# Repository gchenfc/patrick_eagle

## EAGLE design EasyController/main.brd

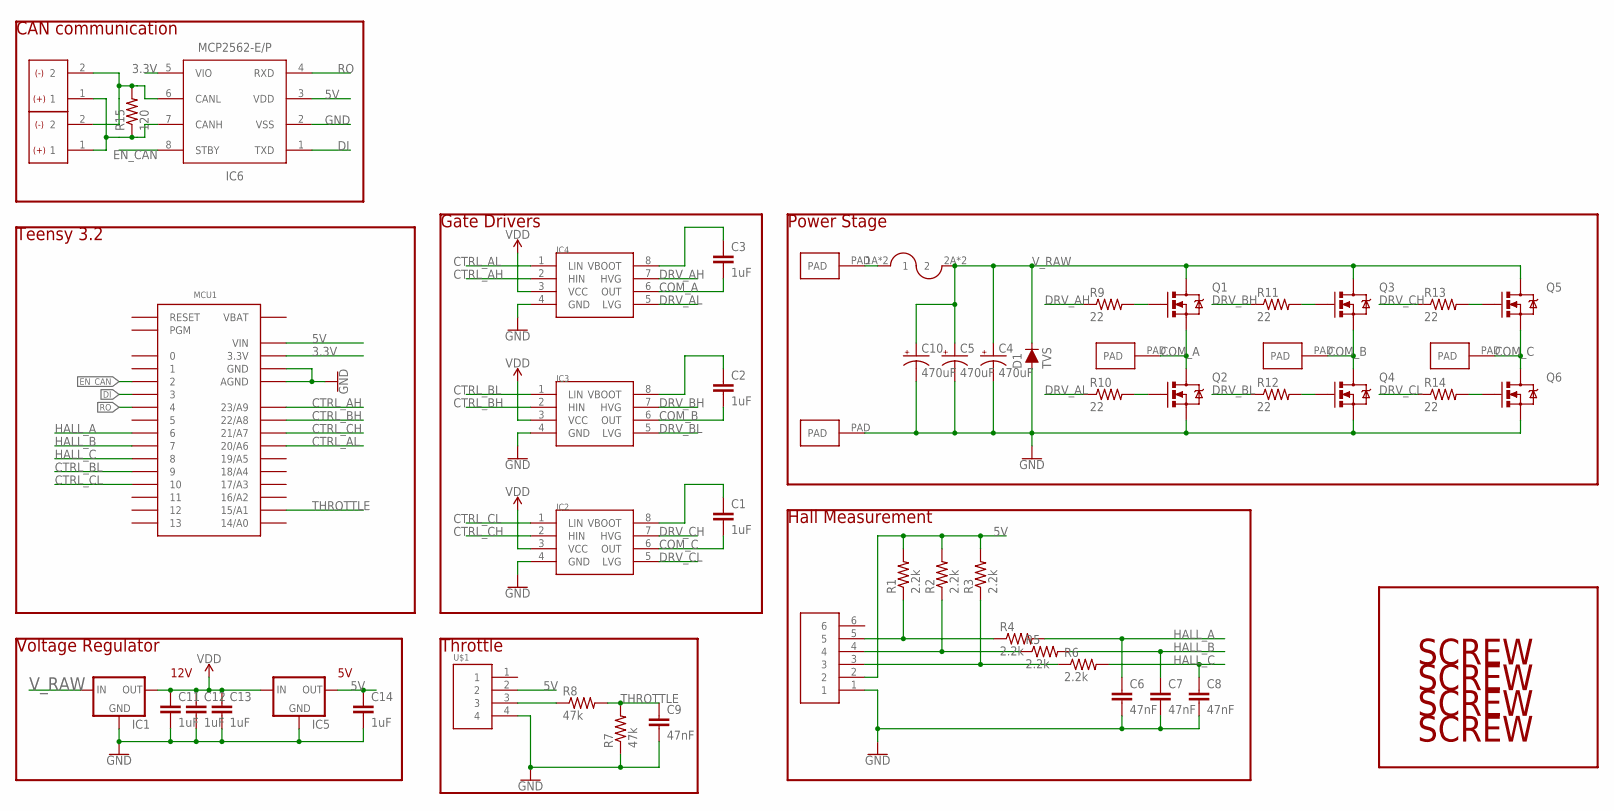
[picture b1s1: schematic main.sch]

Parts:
C1, C2, C3, C11, C12, C13, C14: 1uF; CAP-PTH-SMALL-KIT
C4, C5, C10: 470uF; CPOL-RADIAL-5MM-10MM
C6, C7, C8, C9: 47nF; CAP-PTH-SMALL-KIT
CAN1, CAN2: HEADER2; 2PINVALULOK
D1: TVS; DIODE-1N4001
IC1: V_REG_78XX; V78W_BACKWARDS
IC2, IC3, IC4: L6387EDIP8; DIP762W53P254L1092H508Q8B
IC5: V_REG_78XXTO-92_UNTESTED; TO-92
IC6: MCP2562-E/P; PDIP8_300MC
J3: FUSE; AUTO_FUSE
MCU1: TEENSY_3.0_BASIC
Q1, Q2, Q3, Q4, Q5, Q6: MOSFET-NCHANNELTO-220-FLAT; TO-220-FLAT
R1, R2, R3, R4, R5, R6: 2.2k; AXIAL-0.3
R7, R8: 47k; AXIAL-0.3
R9, R10, R11, R12, R13, R14: 22; AXIAL-0.3
R15: 120; AXIAL-0.3
U$1: HEADER4VALULOK; 4PINVALULOK
U$2: HEADER6; 6PINVALULOK
U$4, U$5, U$6, U$7, U$8: PAD
U$10, U$11, U$12, U$13: SCREW; M3HOLE

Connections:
3.3V: IC6.5 (VIO), MCU1.3.3V, MCU1.3.3V1 (3.3V)
5V: C14.1, IC5.1 (OUT), IC6.3 (VDD), MCU1.VIN, R1.P$2 (2), R2.P$2 (2), R3.P$2 (2), U$1.2, U$2.2
CANH: CAN1.1, CAN2.1, IC6.7 (CANH), R15.P$1 (1)
CANL: CAN1.2, CAN2.2, IC6.6 (CANL), R15.P$2 (2)
COM_A: C3.2, IC4.6 (OUT), Q1.3 (S), Q2.2 (D), Q2.PAD (D), U$6.PAD
COM_B: C2.2, IC3.6 (OUT), Q3.3 (S), Q4.2 (D), Q4.PAD (D), U$7.PAD
COM_C: C1.2, IC2.6 (OUT), Q5.3 (S), Q6.2 (D), Q6.PAD (D), U$8.PAD
CTRL_AH: IC4.2 (HIN), MCU1.23/A9
CTRL_AL: IC4.1 (LIN), MCU1.20/A6
CTRL_BH: IC3.2 (HIN), MCU1.22/A8
CTRL_BL: IC3.1 (LIN), MCU1.9
CTRL_CH: IC2.2 (HIN), MCU1.21/A7
CTRL_CL: IC2.1 (LIN), MCU1.10
DI: IC6.1 (TXD), MCU1.3
DRV_AH: IC4.7 (HVG), R9.P$1 (1)
DRV_AL: IC4.5 (LVG), R10.P$1 (1)
DRV_BH: IC3.7 (HVG), R11.P$1 (1)
DRV_BL: IC3.5 (LVG), R12.P$1 (1)
DRV_CH: IC2.7 (HVG), R13.P$1 (1)
DRV_CL: IC2.5 (LVG), R14.P$1 (1)
EN_CAN: IC6.8 (STBY), MCU1.2
GND: C4.-, C5.-, C6.2, C7.2, C8.2, C9.2, C10.-, C11.2, C12.2, C13.2, C14.2, D1.A, IC1.GND, IC2.4 (GND), IC3.4 (GND), IC4.4 (GND), IC5.2 (GND), IC6.2 (VSS), MCU1.AGND, MCU1.GND, MCU1.GND1 (GND), Q2.3 (S), Q4.3 (S), Q6.3 (S), R7.P$1 (1), U$1.4, U$2.1, U$5.PAD
HALL_A: C6.1, MCU1.6, R4.P$2 (2)
HALL_B: C7.1, MCU1.7, R5.P$2 (2)
HALL_C: C8.1, MCU1.8, R6.P$2 (2)
unnamed: C1.1, IC2.8 (VBOOT)
unnamed: R3.P$1 (1), R6.P$1 (1), U$2.3
unnamed: C2.1, IC3.8 (VBOOT)
unnamed: R2.P$1 (1), R5.P$1 (1), U$2.4
unnamed: C3.1, IC4.8 (VBOOT)
unnamed: R1.P$1 (1), R4.P$1 (1), U$2.5
unnamed: R8.P$1 (1), U$1.3
unnamed: Q1.1 (G), R9.P$2 (2)
unnamed: Q2.1 (G), R10.P$2 (2)
unnamed: Q3.1 (G), R11.P$2 (2)
unnamed: Q4.1 (G), R12.P$2 (2)
unnamed: Q5.1 (G), R13.P$2 (2)
unnamed: Q6.1 (G), R14.P$2 (2)
RO: IC6.4 (RXD), MCU1.4
THROTTLE: C9.1, MCU1.15/A1, R7.P$2 (2), R8.P$2 (2)
VBAT: MCU1.VBAT
VDD: C11.1, C12.1, C13.1, IC1.OUT, IC2.3 (VCC), IC3.3 (VCC), IC4.3 (VCC), IC5.3 (IN)
V_PREFUSE: J3.1A (1), J3.1B (1), U$4.PAD
V_RAW: C4.+, C5.+, C10.+, D1.C, IC1.IN, J3.2A (2), J3.2B (2), Q1.2 (D), Q1.PAD (D), Q3.2 (D), Q3.PAD (D), Q5.2 (D), Q5.PAD (D)

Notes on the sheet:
Power Stage
Hall Measurement
Gate Drivers
Throttle
Teensy 3.2
Voltage Regulator
12V
CAN communication

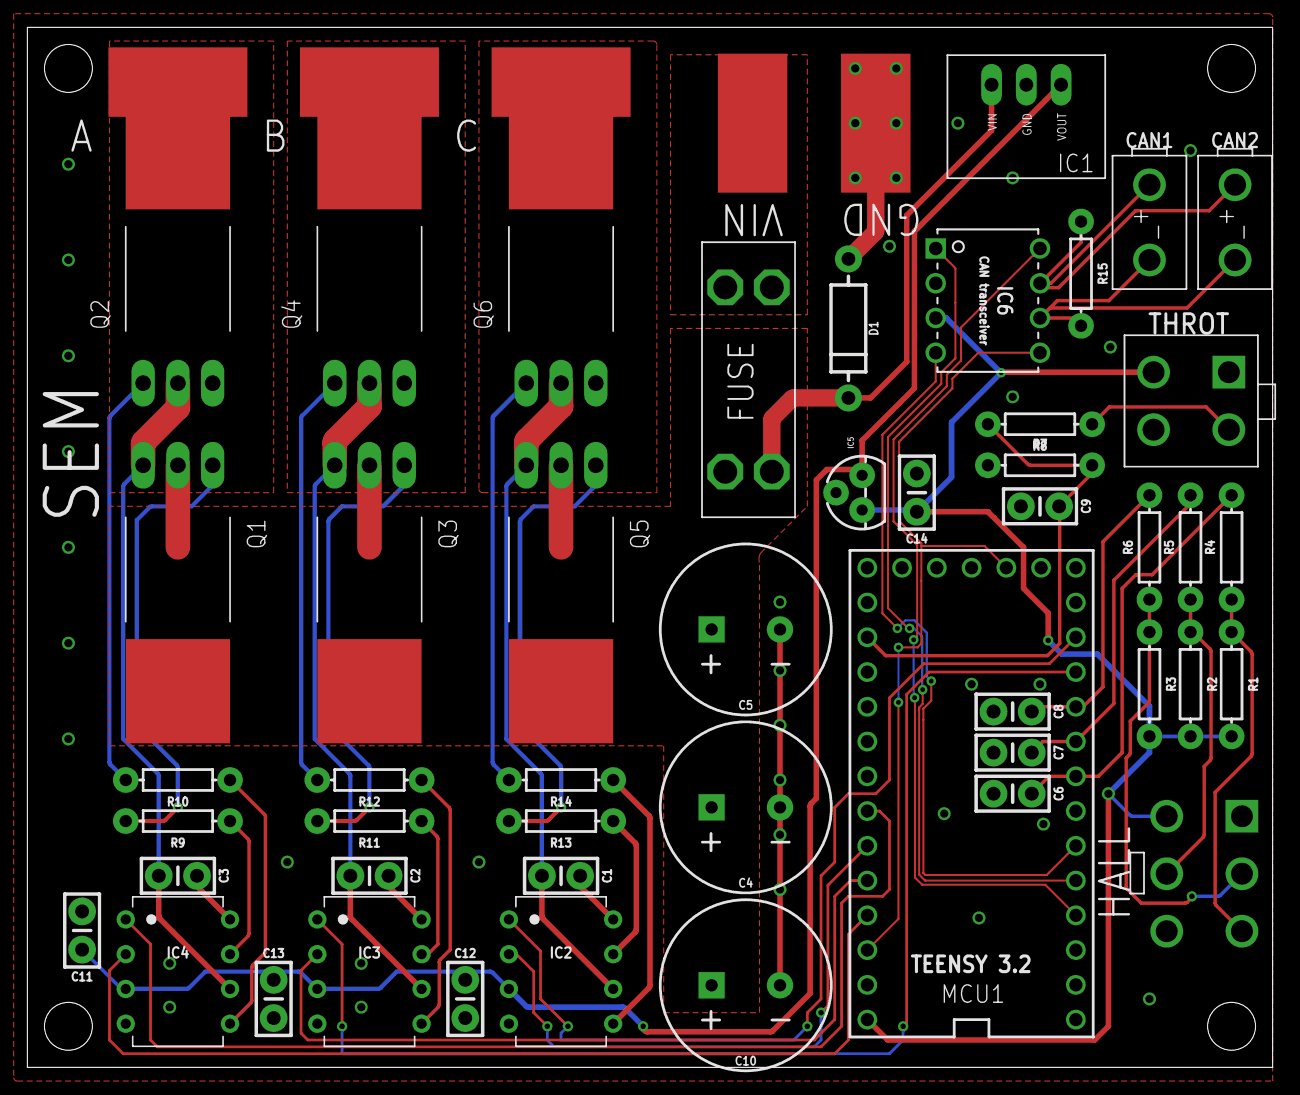
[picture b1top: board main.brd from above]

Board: 2 copper layers, 91.0 x 76.0 mm, 59 parts (1 on the bottom side), 43 nets.

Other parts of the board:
U$3, U$9: DEV

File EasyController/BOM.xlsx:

Digikey part # | Designator | Qty | Price | Description
497-6219-5-ND | IC2,IC3,IC4 | 3 | 1.66 | Gate driver |  |  |  | 4.9799999999999995 |  | 69.429999999999964
445-173257-1-ND | C1,C2,C3,C11,C12,C13,C14 | 7 | 0.33 | 1uF cap |  |  |  | 2.31
IRFB7730PBF-ND | Q1,Q2,Q3,Q4,Q5,Q6 | 6 | 3.51 | NFET |  |  |  | 21.06
P6KE68CALFCT-ND | D1 | 1 | 0.47 | TVS Diode |  |  |  | 0.47
565-3994-ND | C4,C5,C10 | 3 | 1.1499999999999999 | 470uF cap |  |  |  | 3.4499999999999997
CF14JT2K20CT-ND | R1,R2,R3,R4,R5,R6 | 6 | 0.1 | 2.2k resistor |  |  |  | 0.60000000000000009
BC1082CT-ND | C6,C7,C8,C9 | 3 | 0.16 | 47nF cap |  |  |  | 0.48
36-3557-2-ND | J3 | 1 | 1.03 | Fuse holder |  |  |  | 1.03
1470-4533-ND | IC1 | 1 | 8 | Voltage Regulator |  |  |  | 8
CF14JT47K0CT-ND | R7,R8 | 1 | 0.1 | 47k resistor |  |  |  | 0.1
1568-1231-ND | MCU1 | 1 | 22.5 | Teensy 3.2 |  |  |  | 22.5
CF14JT22R0CT-ND | R9,R10,R11,R12,R13,R14 | 6 | 0.1 | 22 ohm |  |  |  | 0.60000000000000009
497-1184-1-ND | IC5 | 1 | 0.35 | 5V Linear reg |  |  |  | 0.35
S1012EC-14-ND |  | 2 | 0.31 | 14 pin male header |  |  |  | 0.62
S7012-ND |  | 2 | 0.91 | 14 pin female header |  |  |  | 1.82
MCP2562-E/P-ND | IC6 | 1 | 0.96 | CAN transceiver |  |  |  | 0.96
CF14JT120RCT-ND | R15 | 1 | 0.1 | 120 resistor |  |  |  | 0.1
345-1092-ND‎ |  | 6 |  | Heatsink
‎1168-1380-ND‎ |  | 1 |  | Thermal paste

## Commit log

2019-03-16 CAN transceiver
2019-03-16 order v1.2

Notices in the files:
parts and their libraries:
SparkFun-Capacitors: Licensing: Creative Commons ShareAlike 4.0 International - https://creativecommons.org/licenses/by-sa/4.0
